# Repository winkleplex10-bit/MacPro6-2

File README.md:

# MacPro6,2

An open PCB redesign of the Mac Pro (Late 2013, "trashcan"). It keeps the enclosure, the triangular thermal core, the fan and the stock 450 W PSU, and replaces every board with new ones.

- `docs/`: the architecture spec (v0.2), the face module spec, the lineup research, the stock hardware reference and the service references
- `kicad/`: KiCad projects (the round base board/backplane, the CPU carrier fallback)
- `mechanical/`: board outlines (DXF), scan traces and 3D-print test parts

Status: early design. The CPU board is our own LGA1700 socket board with an Apple-style contact frame. The faces are an open module spec (GPU on Face P, storage on Face S).

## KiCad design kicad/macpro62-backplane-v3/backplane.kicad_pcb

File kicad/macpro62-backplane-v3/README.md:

# MacPro6,2 backplane (BP) - KiCad 9 project, rev v3 (6 layers, slot B x4; rev A1 4L history below)

## Rev v3 (2026-10-09, routed on 6 layers, slot B full x4)

- **Stackup:** 6L JLC06161H-2116, 1.6 mm, ENIG. Layers: L1 `L1_SIG_RX` (RX microstrip), L2 `L2_GND`, L3 `L3_SIG_TX_PWR` (TX stripline + `L3_3V3_SB` plane, y >= 116.2), L4 `L4_SIG_SLOTB` (new slot-B layer), L5 `L5_GND`, L6 `L6_GND_BRK` (GND + low-speed breakout). Through vias 0.45 / 0.25 only. Clearance 0.1 mm (0.15 mm for power).
- **Impedance** (`docs/impedance_v3_6L.json`, `tools/zsolve.py`):
  - L1/L6 85 Ω pairs: 85.5 Ω (w 0.26 / gap 0.125).
  - Existing v1 L3 TX pairs keep their geometry: 88.7–89.7 Ω, within ±10 %.
  - New L3/L4 pairs: 84.5–85.7 Ω (w 0.24 / gap 0.127).
- **Slot B (J1 → J10), lanes 4–7 + REFCLK1.** Intra-pair skew is 0.000 mm on all nine pairs, with 0 P/N issues (`work/pairchk.py`). Length per net and vias per net:

  | Pair | Length (mm) | Vias per net |
  |---|---|---|
  | REFCLK1 | 32.34 | 4 |
  | RX4 | 38.94 | 0 |
  | RX5 | 69.75 | 3 |
  | RX6 | 44.75 | 0 |
  | RX7 | 40.09 | 2 |
  | TX4 | 49.53 | 3 |
  | TX5 | 57.46 | 3 |
  | TX6 | 65.02 | 4 |
  | TX7 | 42.54 | 2 |

- **Broadside rule:** no low-speed track on L3 sits over L4 high-speed copper, and none on L4 sits under L3 high-speed copper (overlap 0, `work/bside.py`).
- **Copper carried over from v1:** v1 HS/SATA/USB2 copper is item-for-item identical to the slot-B build (v6_E8). The v1 48-pair skew table is unchanged (`work/skew_v1_baseline.txt`).
- **Status:**
  - `backplane.kicad_pcb`: **DRC 0 violations, 0 unconnected, 0 schematic-parity issues** (`drc_report.txt`).
  - **ERC: 0 errors / 0 warnings** (`erc_report.txt`).
  - JLC outputs in `jlc/`: 18 Gerber/drill files (6 copper layers), 44 BOM lines, 143 placed parts, all on F.
  - New parts vs A1: Q12 2N7002, R64 1 k, R65 10 k.
- **Low-speed flow:** the low-speed copper was rebuilt as follows. Step log: `PROGRESS_V3.md`.
  1. Freerouting runs, using `tools/bp_ls6.py` (the `L25=` option allows local L2/L5 routing with 0.6 mm clearance to HS copper).
  2. Single-net clean-up with `tools/bp_fix.py` and `work/reach.py`, a 0.1 mm grid min-cost router.
  3. `bp_post.sh`.
  4. DRC fix-ups, one net at a time.
- **Needs Aidan's approval before ordering:**
  - ICD 3.1 FS-lane reversal.
  - INA226 replacing INA228.
  - J7 M.2 DNP, which sets the BIOS/OpenCore boot location.
  - R27 → R33.
  - RP2350B GPIO re-map (firmware pin-map update, `tools/gpio_map.json`).
  - The U1 / Y1 / U2 moves.
  - Storage-face deviations: D-2X-1 and D-2X-2 (pending), and D-S1.
- **Interface:** ICD v3 is `/workspace/macpro62-interface-control-v3.md` (13 reserved pins).
- **Cost:** `/workspace/macpro62-cost-estimate.md` §11. Excluding the CPU, the change is about +$25–35 (6L fab). Including the CPU, it is about −$52 to +$102.
- **Previews:** `docs/preview_v3_L1.png`, `docs/preview_v3_L3.png`, `docs/preview_v3_L4.png`, `docs/preview_v3_L6.png`.

## Rev A1 (2026-10-04, routed on 4 layers)

- **Stackup:** 4L JLC04161H-7628, 1.6 mm, ENIG (was 6L JLC06161H-2116). L1 `L1_SIG_RX` (host RX, microstrip 85 Ω, 83.1 Ω calc), L2 `L2_GND`, L3 `L3_SIG_TX_PWR` (host TX stripline 86.4 Ω + `L3_3V3_SB` plane), L4 `L4_GND_BRK` (GND + low-speed breakout). Through vias 0.45 / 0.25 only. Impedance: `docs/impedance_A1.json`; loss budget: `docs/loss_budget_A1.md`. Gen5 redrivers removed (Gen4 loss 9.5–16.8 dB of 28 dB).
- **Status:** `backplane.kicad_pcb` **DRC 0 violations, 0 unconnected, 0 schematic-parity issues** (`drc_report.txt`); **ERC 0 errors / 0 warnings** (`erc_report.txt`). JLC outputs in `jlc/` (16 Gerber/drill files, 44 BOM lines, 140 placed parts, all on F; 152 footprints incl. 9 DNP).
- **High-speed pairs:** all 40 FP/FS PCIe pairs (x16 + x4, TX and RX) + FP/FS REFCLK: intra-pair skew 0.000 mm, 2 vias per net (J1 escape + one layer change). **SATA0_RX** (J7 41/43 → J1): coupled 85 Ω pair, L1 → L3, 29.45 / 29.45 mm, 2/2 vias. **SATA0_TX** (J7 47/49 → J1 A73/A74): coupled pair, L1 stubs → L3 → L1, 27.70 / 27.70 mm, 2/2 vias. **USB2_SPARE** (J1 B79/B80 → J6 13/14): coupled 90 Ω pair, 57.04 / 57.04 mm, 4/4 vias (was 15/12). USB2 (net-by-net routed, skew incl. 1.6 mm per via): USB2_FACEP 78.6/78.3 mm, skew 0.34 mm, 2/2 vias; USB2_FACES 118.0/114.8 mm, skew 0.00 (4/6 vias); USB2_MCU 28.7/28.3 mm, skew −2.7 mm (3/5 vias, could not reach ≤ 1.5 mm).
- **Flow (tools/):** `build_bp.py` → `bp_hs.py` (HS patterns) → `bp_tune.py` (skew → 0; `TUNE_RE`) → Freerouting (low-speed) → `bp_fix.py route` (grid A* clean-up; footprint/board keep-outs dilated `KOD`, NPTH clearance `NPTHC`, SATA/USB2_SPARE protected via `HSX`; `drcfix` mode removes DRC-violating copper) → `bp_pair.py` (coupled-pair centre-line A* router, `PAIR=RX|TX|USB2_SPARE`) and `bp_hand.py` (hand-route spec with clearance check) → `bp_post.sh` / `bp_finish.py` (pours, GND fan-out, DRC) → `bp_clean2.py` (in-process dangling clean-up, refills first) / `bp_island.py` (GND island stitch vias) / `bp_fill.py` → `jlc_out.py`. Skew report `bp_skew.py`, zone report `bp_zreport.py`. Step log: `PROGRESS_A1.md`.
- **Needs Aidan's approval before ordering:** ICD 3.1 FS-lane reversal; INA226 replacing INA228; J7 M.2 DNP (and so the BIOS/OpenCore boot location); R27 → R33; RP2350B GPIO re-assignment (**firmware pin-map update needed**, `tools/gpio_map.json`); the U1 / Y1 / U2 moves.
- Cost: `/workspace/macpro62-cost-estimate.md` §6a (BP q1 $285–450 → $145–230, q5 $450–750 → $260–395).
- Previews: `docs/preview_A1_L1.png` (L1), `docs/preview_A1_L3.png` (L3) (also in `work/`).

## History (floorplan revisions)

Topology: **HUB** (Aidan, 2026-10-01). The CPU board plugs into J1 (Amphenol Mini Cool Edge 224, ME1022410103011, vertical SMT) and the BP routes PCIe x16 to J9 (MCIO 124, Face P) and x4 to J10 (MCIO 124, Face S).

**Floorplan rev A-fp3 (2026-10-01):** uses Aidan's measurements M1 (GPU-board bottom edges ~15 mm above the BP) and M2 (GPU-board planes ~55 mm from the centre). J9/J10 are now **right-angle** MCIO 124 placeholders (`MP62_MCIO_124P_RightAngle_SMT_PLACEHOLDER`, est. ~9-10 mm high; straight plugs are 15.90 mm and do not fit) with the cable exiting radially under each face edge. J1 sits at the **estimated stock riser-slot chord y = -12.6** (TBD, M2b). The M.2, power and harness connectors moved to the PSU side (-y). The previous fp2 (d = 30 assumed) is archived in `variants/hub_fp2_d30_assumed/`.
**fp3a (2026-10-01, CPU-carrier cross-check):** the J1 placeholder had contact A1 at +x with the A row toward +y, which no real Mini Cool Edge has (top view, A row up: A1 is at -x). The placeholder now uses the real contact offsets from the Amphenol card drawing (incl. key F), and **J1 is rotated 180 deg**: A1 stays at disc +x (bay -> face mapping unchanged), the **A row (host TX) faces the PSU side** and the B row (host RX) faces the core. Layer use swaps: host RX on L1, host TX via to L6. Mates `/workspace/kicad/macpro62-cpu-carrier/` J1 fingers. The pre-fix state is in `/workspace/scratch/bp_before_fp3a/`.

**fp6 (2026-10-04 ≈ 09:10 ET, ICD rev 3, O-10 approved by Aidan):** zero-jog straight-straight MCIO cable with **narrow plugs**.
- `tools/hub_floorplan.py`: **J9 r_c 31.2 → 33.0, s −5.2 → +5.0** (origin (20.62, 13.27) → (14.68, 21.75), ≈ 10.4 mm); **J10 r_c 31.5 → 29.5, s −2.0 → +5.0** (origin (−15.74, 18.57) → (−19.28, 12.20), ≈ 7.3 mm). s = +5.0 = module J_PCIE X 47.0 (face spec update 6), so neither cable jogs. Narrow-plug courtyard (±21.6, `make_footprints.py` in the face template): J9–J10 gap 4.28 mm, **J1–J10 2.33 mm**, J1–J9 11.88 mm.
- **J3 (Face P AUX) (0, 51.4) rot 0 → (42.5, 13.5) rot 45** (≈ 55 mm; beyond J9's outer end, Face-P s ≈ −20.5) and **J4 (Face S AUX) (−38.0, 2.5) rot 135 → (−2.5, 43.5) rot 45** (≈ 54 mm; apex wedge, Face-S s ≈ −28.6). A full free-space search found no other GH15 site; each AUX cable runs along its own face's bottom edge above the MCIO ribbon (≈ 56 mm lateral Face P, ≈ 64 mm Face S; lengths M9).
- **U3 (0, 41.6) → (−7.5, 49.0)** (≈ 10.5 mm). Redriver row **U10–U14 +2.5 mm in x** (U14 (−19.35, −3.5) → (−16.85, −3.5), 0.51 mm to J10).
- New F.Cu rule areas `MCIO_RIBBON_J9` / `MCIO_RIBBON_J10` (no footprints/pads) from the courtyard outer edge to n 63, s ± 21.6.
- Not routed (placeholders only), so nothing to re-route. Fit check ALL OK (27 parts), **DRC 0 violations / 0 unconnected**. System fit check `tools/fitcheck_o10.py` → `fitcheck_mcio_o10.txt` (ALL OK; notes: bend beyond the BP rim r ≤ 65.8 → base ring M1b; S5 under the J9 ribbon, CR-BP-1). Previous fp5 board/scripts: `/workspace/scratch/o10/`.

**fp5 (2026-10-02 ≈ 13:15 ET, ICD rev 2, Aidan: face normals ≈ 45° / 135°):**
- `tools/hub_floorplan.py` (`FACE_P_ANG` / `FACE_S_ANG`): J9 at r_c 31.2, s −5.2, rot −45°; J10 at r_c 31.5, s −2.0, rot +45° (apex gap 1.3 mm). At 90° between faces both receptacles cannot sit at s = +8.5 (they collide at the apex; J10 is bounded by the G1 keep-out), so **CR-2 is closed by a flat-twinax jog cable** (jogs 13.7 / 10.5 mm, face spec §3.6, feasibility ICD O-6).
- J3 (0, 51.4) apex wedge; J4 (−38.0, 2.5) rot 135° beyond J10's lower-left end (6.3 mm from G1). Redrivers U10–U14, U1 (0, 15.3), U2 (−9, 6), Y1 (−2.6, 6), U3 (0, 41.6) re-packed in the V; SW1 (30.5, −34) and J8 (−40, −34) moved to the PSU side.
- `build_pcb.py` chords at 45° / 135°; drawings (corridors, plane triangle incentre (0, 24.8), lane estimate Face P 39–65 mm / Face S 40–43 mm) updated.
- CPU-LINK **A105 = PWR_ALERT#** (was RSVD_LS1; CB INA228 + eFuse FLT#, BP 10k pull-up); schematic stubs `MOD_PWR_ALERT_N`, `PWR_ALERT_BP_N`, BP INA228 0x40 note, LPT + EMC2101 reload text on the MCU sheet.
- Fit check ALL OK (27 parts, max r 57.8), DRC 0/0, ERC 0.

**fp4 (2026-10-02, interface audit, `/workspace/macpro62-interface-control.md`):**
- **CR-BP-1 applied:** the six small stock holes S1-S6 (base-board scan, `bracket/base_board/`) get D6 rule-area keep-outs (`CR-BP-1_KO_S1..S6`, all copper layers, no footprints/tracks/vias/pours) and are part of the fit check (courtyard >= 3.0 mm from each S centre). **U4** moved from (-27, -46.5) (S2 inside its courtyard) to (-30, -38). **J6** moved to x 11.4 (S3), **J3** to the apex V at (0, 51) rot 0 and **J4** parallel to the J10 inner side at (-15.9, 14.95) rot 60 (S4/S5 and the new J9 position); **J8** SWD to (0, 44.6), **U3** to (0, 39.8), **Y1** to (-6.4, 14.0).
- **J3/J4 are GH 15P** (`JST_GH_BM15B-GHS-TBT`, face spec C-4: pin 15 MOD_LED#, pins 13/14 USB2 primary); pinout 1:1 with `macpro62-face/pinouts/mp62-face-v0.1_aux_gh15.csv`.
- **J9/J10 use the SFF-TA-1016 RA footprint** `MP62_MCIO_124P_RA_SFF-TA-1016` (copied from the face template by `make_placeholders.py`). CR-2 (s = +8.5 on both faces) is **only partly possible**: J9 at s = +8.0 / r_c 36.5 (0.5 mm short, S5 keep-out); J10 at s > -4.6 enters the G1 gold-hole keep-out (6 mm), so it stays at s = -5.0 / r_c 37.2 and the **Face S cable needs a 13.5 mm lateral jog** (open decision, ICD O-1).
- **J5 (fan GH4) removed:** the fan is driven by the IOB EMC2101 (0x4C, I2C_SYS) on IOB CONN_C; the BP MCU writes the CB fan demand (CPU-LINK FAN_PWMOUT) to it. `fan.kicad_sch` deleted.
- **Schematic stubs** gained IOB-LINK `IOB_INT_N`, `IOB_PRSNT_N`, `IOB_USB_DP/DN` (CPU-LINK USB2_SPARE), face `MOD_LED_N`, CPU-LINK `MOD_I2C0` (CB ID EEPROM 0x57); each stub sheet now holds one non-BOM `#BLKn` symbol (passive pins, `MP62_BP_Stubs.kicad_sym`) so **ERC is 0 violations**.
- `docs/cpulink_224_pinout_draft.csv` has a **CB mapping column** (LGA1700/Z790 PCH + RP2350 EC net, direction seen from the CB).

Spec: `/workspace/macpro62-architecture-spec-v0.2.md` (sections 3 and 4.9). Interfaces: `/workspace/macpro62-interface-control.md`.

| File | What |
|---|---|
| `backplane.kicad_pcb` / `.kicad_pro` | HUB floorplan, 6 layers, JLC06161H-2116 stackup, placeholders only (not routed) |
| `floorplan.png` / `.svg` | Render of the hub floorplan |
| `drc_report.txt` | `kicad-cli pcb drc --severity-all`: 0 violations, 0 unconnected |
| `fitcheck_floorplan.txt` | r_max <= 58 mm, gold-hole distance >= 6 mm and S1-S6 distance >= 3 mm per footprint |
| `fitcheck_mcio_o10.txt` | O-10 system fit check (`tools/fitcheck_o10.py`, system python3): zero jog, J1 clearance, ribbon corridors, cable lengths, face envelope, SM-1 |
| `lane_length_estimate.txt` | Estimated BP PCIe lane lengths (J1 -> MCIO) |
| `docs/cpulink_224_pinout_draft.csv` | CPU-LINK 224 pin list draft with the CB mapping (from `tools/cpulink_pinout.py`) |
| `backplane_direct.kicad_pcb` | Saved DIRECT variant (4L JLC04161H-7628, no PCIe on BP) |
| `variants/` | Direct fit check, DRC and render; archived all-MCIO hub fit check; `hub_fp2_d30_assumed/` (previous hub floorplan) |
| `backplane.kicad_sch` + sheets | Block-diagram stubs (hierarchical labels + non-BOM stub symbols); `erc_report.txt`: 0 violations |
| `MP62_Placeholders.pretty/` | Placeholder footprints (outer dimensions from vendor drawings) + the SFF-TA-1016 MCIO RA footprint |
| `MP62_BP_Stubs.kicad_sym`, `sym-lib-table` | Stub symbols written by `tools/build_sch.py` |

Rebuild (from this folder):

```
python3 tools/make_placeholders.py
rm -f backplane.kicad_pcb backplane.kicad_pro backplane.kicad_prl
python3 tools/build_pcb.py          # VARIANT=direct for backplane_direct.kicad_pcb
python3 tools/postprocess.py        # VARIANT=direct for the 4L stackup
kicad-cli pcb drc --severity-all -o drc_report.txt backplane.kicad_pcb
tools/render.sh backplane.kicad_pcb floorplan
python3 tools/fitcheck_o10.py       # needs ../macpro62-face-template and ../macpro62-storage-face
python3 tools/cpulink_pinout.py
python3 tools/build_sch.py
kicad-cli sch erc --severity-all -o erc_report.txt backplane.kicad_sch
```

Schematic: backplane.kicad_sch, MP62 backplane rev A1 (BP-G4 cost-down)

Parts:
C1, C5, C8, C9, C12, C14, C16, C19, C21, C22, C23, C24, C25, C26, C27, C28, C32, C33, C34, C35, C38, C39: 100nF 16V X7R 0402; C_0402_1005Metric; LCSC C1525
C2, C3, C4, C6, C7, C10, C11, C13, C15: 22uF 25V X5R 0805; C_0805_2012Metric; LCSC C45783
C17: 22uF 25V X5R 0805; C_0805_2012Metric; LCSC C45783; not fitted
C18: 100nF 16V X7R 0402; C_0402_1005Metric; LCSC C1525; not fitted
C20: 1uF 25V X5R 0402; C_0402_1005Metric; LCSC C52923
C29, C30, C31: 4.7uF 10V X5R 0402; C_0402_1005Metric; LCSC C23733
C36, C37: 15pF 50V C0G 0402; C_0402_1005Metric; LCSC C1548
D1, D2: SS34 3A 40V Schottky SMA; D_SMA; LCSC C8678
D3: SMAJ15A TVS SMA; D_SMA; LCSC C113958
D4, D5: BAT54A (LBAT54ALT1G); SOT-23; LCSC C12743
D6, D7, D8, D9, D10: LED red 0603; LED_0603_1608Metric; LCSC C2286
F1: 3A 1206 fast fuse (0466003.NRHF class); Fuse_1206_3216Metric; LCSC C14165
H1, H2: MountingHole D4 plated (GND); MountingHole_4mm_Pad
H3: M.2 2242 standoff pad (DNP option); MP62_M2_Standoff_SMT_M2_Pad5.0; not fitted
J1: ME1022410103011 Mini Cool Edge 224 (C4941560, 0 s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; MP62_CPULINK_MiniCoolEdge_224P_Vertical_SMT_PLACEHOLDER; LCSC C4941560
J2: Molex 43045-0812 Micro-Fit 2x4 (C277661); Molex_Micro-Fit_3.0_43045-0812_2x04_P3.00mm_Vertical; LCSC C277661
J3: BM15B-GHS-TBT (C5305069) Face P AUX; JST_GH_BM15B-GHS-TBT_1x15-1MP_P1.25mm_Vertical; LCSC C5305069
J4: BM15B-GHS-TBT (C5305069) Face S AUX; JST_GH_BM15B-GHS-TBT_1x15-1MP_P1.25mm_Vertical; LCSC C5305069
J6: BM15B-GHS-TBT (C5305069) IOB-LINK; JST_GH_BM15B-GHS-TBT_1x15-1MP_P1.25mm_Vertical; LCSC C5305069
J7: M.2 M-key socket LOTES APCI0107 class (C841661) -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; MP62_M2_MKey_SMT_H4.2_PLACEHOLDER; LCSC C841661; not fitted
J8: BM03B-SRSS-TB SWD (DNP); JST_SH_BM03B-SRSS-TB_1x03-1MP_P1.00mm_Vertical; LCSC C160389; not fitted
J9: MCIO 124P RA G97R24332HR class (C4867471, 0 stock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; MP62_MCIO_124P_RA_SFF-TA-1016; LCSC C4867471
J10: MCIO 124P RA (C4867471) -> Face S x4 + slot B x4 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; MP62_MCIO_124P_RA_SFF-TA-1016; LCSC C4867471
JP1: BENCH: bridges the Hall interlock (open = normal); SolderJumper-2_P1.3mm_Open_RoundedPad1.0x1.5mm
L1, L2: 4.7uH 2A 4x4 (SWPA4030S4R7MT); L_Changjiang_FNR4030S; LCSC C57269
L3: 3.3uH 0806 (FNR201610S3R3MT, RP2350 VREG); L_0805_2012Metric; LCSC C167673
Q1, Q2, Q5, Q6, Q7, Q8: AO3401A P-MOS; SOT-23; LCSC C15127
Q3: AO3401A P-MOS; SOT-23; LCSC C15127; not fitted
Q4: 2N7002 N-MOS; SOT-23; LCSC C8545; not fitted
Q9, Q10, Q11, Q12: 2N7002 N-MOS; SOT-23; LCSC C8545
R1: 33k 1% 0402; R_0402_1005Metric; LCSC C25779
R2, R4, R7, R8, R13, R14, R15, R16, R17, R18, R19, R20, R21, R23, R24, R25, R26, R29, R30, R33, R34, R35, R36, R39, R40, R42, R43, R44, R45, R46, R47, R48, R49, R65: 10k 1% 0402; R_0402_1005Metric; LCSC C25744
R3: 56k 1% 0402; R_0402_1005Metric; LCSC C25796
R5: 100k 1% 0402 (U6 EN, always on); R_0402_1005Metric; LCSC C25741
R6: 100k 1% 0402 (U7 off until the MCU enables 5V_SBY); R_0402_1005Metric; LCSC C25741
R9, R10: 10k 1% 0402; R_0402_1005Metric; LCSC C25744; not fitted
R11, R12, R55: 100k 1% 0402; R_0402_1005Metric; LCSC C25741
R22, R31, R32, R41, R54, R58, R60, R61, R64: 1k 1% 0402; R_0402_1005Metric; LCSC C11702
R27, R28, R37, R38, R50, R51, R52, R53: 2.2k 1% 0402; R_0402_1005Metric; LCSC C25879
R56: 10k 1% 0402 (12V LED); R_0402_1005Metric; LCSC C25744
R57: 10k 1% 0402 (11V_SB LED); R_0402_1005Metric; LCSC C25744
R59, R62, R63: 33R 1% 0402; R_0402_1005Metric; LCSC C25105
R100: 10mR 1% 1W 1206 shunt; R_1206_3216Metric; LCSC C105362
SW1: BOOTSEL (TS-1187A); SW_Push_1P1T_XKB_TS-1187A; LCSC C318884
SW2: BENCH power button (TS-1187A); SW_Push_1P1T_XKB_TS-1187A; LCSC C318884
U1: RP2350B QFN-80 (C42415655); QFN-80-1EP_10x10mm_P0.4mm_EP3.4x3.4mm; LCSC C42415655
U2: W25Q128JVSIQ (C97521, basic); SOIC-8_5.3x5.3mm_P1.27mm; LCSC C97521
U3: TMP1075DGKR @0x48 core side (C2864807); VSSOP-8_3x3mm_P0.65mm; LCSC C2864807
U4: TMP1075DGKR @0x49 PSU side (C2864807); VSSOP-8_3x3mm_P0.65mm; LCSC C2864807
U5: INA226AIDGSR @0x40 (C49851); VSSOP-10_3x3mm_P0.5mm; LCSC C49851
U6: TPS563201DDCR (C116592) -> 3V3_SB; SOT-23-6; LCSC C116592
U7: TPS563201DDCR (C116592) -> 5V_SBY; SOT-23-6; LCSC C116592
U8: SN74LVC1G74DCUR thermal latch (C70285); VSSOP-8_2.3x2mm_P0.5mm; LCSC C70285
Y1: 12MHz 3225 crystal 20pF; Crystal_SMD_3225-4Pin_3.2x2.5mm; LCSC C9002

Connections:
3V3_AUX_P: C13.1, C14.1, J3.1 (3V3_AUX), J3.2 (3V3_AUX), Q1.3 (D), R26.2, R27.2, R28.2, R29.2, R30.2, R31.2
3V3_AUX_S: C15.1, C16.1, J4.1 (3V3_AUX), J4.2 (3V3_AUX), Q2.3 (D), R36.2, R37.2, R38.2, R39.2, R40.2, R41.2, R65.2
3V3_M2: C17.1, C18.1, J7.2 (3V3), J7.4 (3V3), J7.12 (3V3), J7.14 (3V3), J7.16 (3V3), J7.18 (3V3), J7.70 (3V3), J7.72 (3V3), J7.74 (3V3), Q3.3 (D)
3V3_SB: C1.1, C6.1, C7.1, C19.1, C21.1, C22.1, C23.1, C24.1, C25.1, C26.1, C27.1, C28.1, C29.1, C38.1, D10.2 (A), J1.B107 (3V3_SB), J1.B108 (3V3_SB), J6.1 (3V3_SB), J6.2 (3V3_SB), JP1.1, L1.2, Q1.2 (S), Q2.2 (S), Q3.2 (S), Q5.2 (S), Q6.2 (S), R1.1, R7.2, R8.2, R9.2, R13.2, R14.2, R15.2, R16.2, R17.2, R18.2, R19.2, R20.2, R21.2, R23.2, R24.2, R25.2, R33.2, R34.2, R35.2, R42.2, R43.2, R44.2, R45.2, R46.2, R47.2, R48.2, R49.2, R50.2, R51.2, R52.2, R53.2, R59.1, U1.5 (IOVDD), U1.15 (IOVDD), U1.24 (IOVDD), U1.29 (IOVDD), U1.41 (IOVDD), U1.50 (IOVDD), U1.59 (ADC_AVDD), U1.60 (IOVDD), U1.64 (VREG_VIN), U1.68 (USB_OTP_VDD), U1.69 (QSPI_IOVDD), U1.76 (IOVDD), U2.8 (VCC), U3.8 (V+), U4.7 (A0), U4.8 (V+), U5.6 (VS), U8.8 (VCC)
5V_SBY: C10.1, C11.1, J1.A107 (5V_SBY), J1.A108 (5V_SBY), J1.A110 (5V_SBY), J1.A111 (5V_SBY), J1.B110 (5V_SBY), J1.B111 (5V_SBY), L2.2, R3.1
11V_SB_IN: D2.2 (A), D9.2 (A), J2.7 (11V_SB)
12V_MAIN_IN: D1.2 (A), D8.2 (A), J2.1 (12V_MAIN), J2.2 (12V_MAIN)
AUXP_EN_N: Q1.1 (G), R7.1, U1.37 (GPIO29)
AUXS_EN_N: Q2.1 (G), R8.1, U1.19 (GPIO19)
BOOTSEL_N: R61.2, SW1.1
BP_OTEMP_N: D5.2 (K2), R21.1, U3.3 (ALERT), U4.3 (ALERT)
BST_3V3_SB: C5.1, U6.6 (VBST)
BST_5V_SBY: C9.1, U7.6 (VBST)
CB_CARRIER_HOT_N: J1.A98 (CARRIER_HOT#), R44.1, U1.13 (GPIO14)
CB_FAN_PWM: J1.B96 (FAN_PWMOUT), U1.6 (GPIO8)
CB_FAN_TACH: J1.B98 (FAN_TACHIN), U1.2 (GPIO5)
CB_I2C0_SCL: J1.B90 (I2C0_CLK), R50.1, U1.80 (GPIO3)
CB_I2C0_SDA: J1.B92 (I2C0_DAT), R51.1, U1.79 (GPIO2)
CB_PLTRST_N: J1.A95 (PLTRST#), R22.1, R32.1, R64.1, U1.54 (GPIO43)
CB_PWRBTN_N: J1.B99 (PWRBTN#), R42.1, U1.57 (GPIO46)
CB_PWR_ALERT_N: J1.A105 (PWR_ALERT#), R43.1, U1.12 (GPIO13)
CB_RSMRST_N: J1.A92 (RSMRST_OUT#), U1.16 (GPIO16)
CB_SUS_S3_N: J1.A89 (SUS_S3#), Q4.1 (G), U1.21 (GPIO21)
CB_SUS_S45_N: J1.A90 (SUS_S4_S5#), U1.58 (GPIO47)
CB_THERMTRIP_N: D4.1 (K1), J1.A96 (THERMTRIP#), R18.1
CB_UART0_RX: J1.B95 (UART0_RX), U1.78 (GPIO1)
CB_UART0_TX: J1.B93 (UART0_TX), U1.77 (GPIO0)
CB_VIN_PWR_OK: J1.A93 (VIN_PWR_OK), U1.14 (GPIO15)
CB_WAKE_N: J1.A99 (WAKE0#), J10.A9 (WAKE), J10.A27 (WAKE1)
CC_PRSNT1_N: J1.A1 (CC_PRSNT1#), R45.1, U1.53 (GPIO42)
CC_PRSNT2_N: J1.A112 (CC_PRSNT2#), R46.1, U1.11 (GPIO12)
DVDD: C30.1, C31.1, C32.1, C33.1, C34.1, L3.2, U1.10 (DVDD), U1.32 (DVDD), U1.51 (DVDD), U1.65 (VREG_FB)
EN_3V3: R5.1, U6.5 (EN)
EN_5V: R6.1, U1.40 (GPIO32), U7.5 (EN)
FB_3V3_SB: R1.2, R2.1, U6.4 (VFB)
FB_5V_SBY: R3.2, R4.1, U7.4 (VFB)
FP_HOLD: Q10.1 (G), R23.1, U1.36 (GPIO28)
FP_LEDA: D6.2 (A), R31.1
FP_MCIO_PRSNT_N: J9.B12 (PRSNT), R24.1, U1.47 (GPIO38)
FP_MOD_LED_N: D6.1 (K), J3.15 (MOD_LED#)
FP_PERST_N: J9.B11 (PERST), Q10.3 (D), R22.2
FP_PRSNT_N: J3.4 (FACE_PRSNT#), R25.1, U1.42 (GPIO33)
FP_PWR_EN: J3.5 (FACE_PWR_EN), U1.49 (GPIO40_ADC0)
FP_PWR_GOOD: J3.6 (FACE_PWR_GOOD), R26.1, U1.43 (GPIO34)
FP_REFCLK_N: J1.A52 (FP_REFCLK_N), J9.A12 (REFCLK-)
FP_REFCLK_P: J1.A51 (FP_REFCLK_P), J9.A11 (REFCLK+)
FP_RX0_N: J1.B49 (FP_PER0_N), J9.A3 (PER0N)
FP_RX0_P: J1.B48 (FP_PER0_P), J9.A2 (PER0P)
FP_RX1_N: J1.B46 (FP_PER1_N), J9.A6 (PER1N)
FP_RX1_P: J1.B45 (FP_PER1_P), J9.A5 (PER1P)
FP_RX2_N: J1.B43 (FP_PER2_N), J9.A15 (PER2N)
FP_RX2_P: J1.B42 (FP_PER2_P), J9.A14 (PER2P)
FP_RX3_N: J1.B40 (FP_PER3_N), J9.A18 (PER3N)
FP_RX3_P: J1.B39 (FP_PER3_P), J9.A17 (PER3P)
FP_RX4_N: J1.B37 (FP_PER4_N), J9.A21 (PER4N)
FP_RX4_P: J1.B36 (FP_PER4_P), J9.A20 (PER4P)
FP_RX5_N: J1.B34 (FP_PER5_N), J9.A24 (PER5N)
FP_RX5_P: J1.B33 (FP_PER5_P), J9.A23 (PER5P)
FP_RX6_N: J1.B31 (FP_PER6_N), J9.A33 (PER6N)
FP_RX6_P: J1.B30 (FP_PER6_P), J9.A32 (PER6P)
FP_RX7_N: J1.B27 (FP_PER7_N), J9.A36 (PER7N)
FP_RX7_P: J1.B26 (FP_PER7_P), J9.A35 (PER7P)
FP_RX8_N: J1.B24 (FP_PER8_N), J9.A40 (PER8N)
FP_RX8_P: J1.B23 (FP_PER8_P), J9.A39 (PER8P)
FP_RX9_N: J1.B21 (FP_PER9_N), J9.A43 (PER9N)
FP_RX9_P: J1.B20 (FP_PER9_P), J9.A42 (PER9P)
FP_RX10_N: J1.B18 (FP_PER10_N), J9.A46 (PER10N)
FP_RX10_P: J1.B17 (FP_PER10_P), J9.A45 (PER10P)
FP_RX11_N: J1.B15 (FP_PER11_N), J9.A49 (PER11N)
FP_RX11_P: J1.B14 (FP_PER11_P), J9.A48 (PER11P)
FP_RX12_N: J1.B12 (FP_PER12_N), J9.A52 (PER12N)
FP_RX12_P: J1.B11 (FP_PER12_P), J9.A51 (PER12P)
FP_RX13_N: J1.B9 (FP_PER13_N), J9.A55 (PER13N)
FP_RX13_P: J1.B8 (FP_PER13_P), J9.A54 (PER13P)
FP_RX14_N: J1.B6 (FP_PER14_N), J9.A58 (PER14N)
FP_RX14_P: J1.B5 (FP_PER14_P), J9.A57 (PER14P)
FP_RX15_N: J1.B3 (FP_PER15_N), J9.A61 (PER15N)
FP_RX15_P: J1.B2 (FP_PER15_P), J9.A60 (PER15P)
FP_SMB_ALERT_N: J3.10 (FACE_SMB_ALERT#), R29.1, U1.44 (GPIO35)
FP_SMB_SCL: J3.8 (FACE_SMB_CLK), R27.1, U1.56 (GPIO45)
FP_SMB_SDA: J3.9 (FACE_SMB_DAT), R28.1, U1.55 (GPIO44)
FP_THERM_ALERT_N: J3.11 (THERM_ALERT#), R30.1, U1.23 (GPIO23)
FP_THERM_TRIP_N: D4.2 (K2), J3.12 (THERM_TRIP#), R19.1
FP_TX0_N: J1.A49 (FP_PET0_N), J9.B3 (PET0N)
FP_TX0_P: J1.A48 (FP_PET0_P), J9.B2 (PET0P)
FP_TX1_N: J1.A46 (FP_PET1_N), J9.B6 (PET1N)
FP_TX1_P: J1.A45 (FP_PET1_P), J9.B5 (PET1P)
FP_TX2_N: J1.A43 (FP_PET2_N), J9.B15 (PET2N)
FP_TX2_P: J1.A42 (FP_PET2_P), J9.B14 (PET2P)
FP_TX3_N: J1.A40 (FP_PET3_N), J9.B18 (PET3N)
FP_TX3_P: J1.A39 (FP_PET3_P), J9.B17 (PET3P)
FP_TX4_N: J1.A37 (FP_PET4_N), J9.B21 (PET4N)
FP_TX4_P: J1.A36 (FP_PET4_P), J9.B20 (PET4P)
FP_TX5_N: J1.A34 (FP_PET5_N), J9.B24 (PET5N)
FP_TX5_P: J1.A33 (FP_PET5_P), J9.B23 (PET5P)
FP_TX6_N: J1.A31 (FP_PET6_N), J9.B33 (PET6N)
FP_TX6_P: J1.A30 (FP_PET6_P), J9.B32 (PET6P)
FP_TX7_N: J1.A27 (FP_PET7_N), J9.B36 (PET7N)
FP_TX7_P: J1.A26 (FP_PET7_P), J9.B35 (PET7P)
FP_TX8_N: J1.A24 (FP_PET8_N), J9.B40 (PET8N)
FP_TX8_P: J1.A23 (FP_PET8_P), J9.B39 (PET8P)
FP_TX9_N: J1.A21 (FP_PET9_N), J9.B43 (PET9N)
FP_TX9_P: J1.A20 (FP_PET9_P), J9.B42 (PET9P)
FP_TX10_N: J1.A18 (FP_PET10_N), J9.B46 (PET10N)
FP_TX10_P: J1.A17 (FP_PET10_P), J9.B45 (PET10P)
FP_TX11_N: J1.A15 (FP_PET11_N), J9.B49 (PET11N)
FP_TX11_P: J1.A14 (FP_PET11_P), J9.B48 (PET11P)
FP_TX12_N: J1.A12 (FP_PET12_N), J9.B52 (PET12N)
FP_TX12_P: J1.A11 (FP_PET12_P), J9.B51 (PET12P)
FP_TX13_N: J1.A9 (FP_PET13_N), J9.B55 (PET13N)
FP_TX13_P: J1.A8 (FP_PET13_P), J9.B54 (PET13P)
FP_TX14_N: J1.A6 (FP_PET14_N), J9.B58 (PET14N)
FP_TX14_P: J1.A5 (FP_PET14_P), J9.B57 (PET14P)
FP_TX15_N: J1.A3 (FP_PET15_N), J9.B61 (PET15N)
FP_TX15_P: J1.A2 (FP_PET15_P), J9.B60 (PET15P)
FS_CLKREQ1_N: J10.A26 (CLKREQ1), R65.1
FS_HOLD: Q11.1 (G), Q12.1 (G), R33.1, U1.17 (GPIO17)
FS_LEDA: D7.2 (A), R41.1
FS_MCIO_PRSNT_N: J10.B12 (PRSNT), R34.1, U1.8 (GPIO10)
FS_MOD_LED_N: D7.1 (K), J4.15 (MOD_LED#)
FS_PERST1_N: J10.B29 (PERST1), Q12.3 (D), R64.2
FS_PERST_N: J10.B11 (PERST), Q11.3 (D), R32.2
FS_PRSNT_N: J4.4 (FACE_PRSNT#), R35.1, U1.9 (GPIO11)
FS_PWR_EN: J4.5 (FACE_PWR_EN), U1.1 (GPIO4)
FS_PWR_GOOD: J4.6 (FACE_PWR_GOOD), R36.1, U1.7 (GPIO9)
FS_REFCLK1_N: J1.B102 (FS_REFCLK1_N), J10.A30 (REFCLK1-)
FS_REFCLK1_P: J1.B101 (FS_REFCLK1_P), J10.A29 (REFCLK1+)
FS_REFCLK_N: J1.A71 (FS_REFCLK_N), J10.A12 (REFCLK-)
FS_REFCLK_P: J1.A70 (FS_REFCLK_P), J10.A11 (REFCLK+)
FS_RX0_N: J1.B68 (FS_PER0_N), J10.A3 (PER0N)
FS_RX0_P: J1.B67 (FS_PER0_P), J10.A2 (PER0P)
FS_RX1_N: J1.B65 (FS_PER1_N), J10.A6 (PER1N)
FS_RX1_P: J1.B64 (FS_PER1_P), J10.A5 (PER1P)
FS_RX2_N: J1.B62 (FS_PER2_N), J10.A15 (PER2N)
FS_RX2_P: J1.B61 (FS_PER2_P), J10.A14 (PER2P)
FS_RX3_N: J1.B59 (FS_PER3_N), J10.A18 (PER3N)
FS_RX3_P: J1.B58 (FS_PER3_P), J10.A17 (PER3P)
FS_RX4_N: J1.B83 (FS_PER4_N), J10.A21 (PER4N)
FS_RX4_P: J1.B82 (FS_PER4_P), J10.A20 (PER4P)
FS_RX5_N: J1.B86 (FS_PER5_N), J10.A24 (PER5N)
FS_RX5_P: J1.B87 (FS_PER5_P), J10.A23 (PER5P)
FS_RX6_N: J1.B104 (FS_PER6_N), J10.A33 (PER6N)
FS_RX6_P: J1.B105 (FS_PER6_P), J10.A32 (PER6P)
FS_RX7_N: J1.B55 (FS_PER7_N), J10.A36 (PER7N)
FS_RX7_P: J1.B54 (FS_PER7_P), J10.A35 (PER7P)
FS_SMB_ALERT_N: J4.10 (FACE_SMB_ALERT#), R39.1, U1.52 (GPIO41)
FS_SMB_SCL: J4.8 (FACE_SMB_CLK), R37.1, U1.4 (GPIO7)
FS_SMB_SDA: J4.9 (FACE_SMB_DAT), R38.1, U1.3 (GPIO6)
FS_THERM_ALERT_N: J4.11 (THERM_ALERT#), R40.1, U1.48 (GPIO39)
FS_THERM_TRIP_N: D5.1 (K1), J4.12 (THERM_TRIP#), R20.1
FS_TX0_N: J1.A68 (FS_PET0_N), J10.B3 (PET0N)
FS_TX0_P: J1.A67 (FS_PET0_P), J10.B2 (PET0P)
FS_TX1_N: J1.A65 (FS_PET1_N), J10.B6 (PET1N)
FS_TX1_P: J1.A64 (FS_PET1_P), J10.B5 (PET1P)
FS_TX2_N: J1.A62 (FS_PET2_N), J10.B15 (PET2N)
FS_TX2_P: J1.A61 (FS_PET2_P), J10.B14 (PET2P)
FS_TX3_N: J1.A59 (FS_PET3_N), J10.B18 (PET3N)
FS_TX3_P: J1.A58 (FS_PET3_P), J10.B17 (PET3P)
FS_TX4_N: J1.A83 (FS_PET4_N), J10.B21 (PET4N)
FS_TX4_P: J1.A82 (FS_PET4_P), J10.B20 (PET4P)
FS_TX5_N: J1.A87 (FS_PET5_N), J10.B24 (PET5N)
FS_TX5_P: J1.A86 (FS_PET5_P), J10.B23 (PET5P)
FS_TX6_N: J1.A102 (FS_PET6_N), J10.B33 (PET6N)
FS_TX6_P: J1.A101 (FS_PET6_P), J10.B32 (PET6P)
FS_TX7_N: J1.A55 (FS_PET7_N), J10.B36 (PET7N)
FS_TX7_P: J1.A54 (FS_PET7_P), J10.B35 (PET7P)
GND: C1.2, C2.2, C3.2, C4.2, C6.2, C7.2, C8.2, C10.2, C11.2, C12.2, C13.2, C14.2, C15.2, C16.2, C17.2, C18.2, C19.2, C20.2, C21.2, C22.2, C23.2, C24.2, C25.2, C26.2, C27.2, C28.2, C29.2, C30.2, C31.2, C32.2, C33.2, C34.2, C35.2, C36.2, C37.2, C38.2, C39.2, D3.2 (A), H1.1, H2.1, H3.1, J1.A4 (GND), J1.A7 (GND), J1.A10 (GND), J1.A13 (GND), J1.A16 (GND), J1.A19 (GND), J1.A22 (GND), J1.A25 (GND), J1.A28 (GND), J1.A29 (GND), J1.A32 (GND), J1.A35 (GND), J1.A38 (GND), J1.A41 (GND), J1.A44 (GND), J1.A47 (GND), J1.A50 (GND), J1.A53 (GND), J1.A56 (GND), J1.A57 (GND), J1.A60 (GND), J1.A63 (GND), J1.A66 (GND), J1.A69 (GND), J1.A72 (GND), J1.A75 (GND), J1.A78 (GND), J1.A81 (GND), J1.A84 (GND), J1.A85 (GND), J1.A88 (GND), J1.A91 (GND), J1.A94 (GND), J1.A97 (GND), J1.A100 (GND), J1.A103 (GND), J1.A106 (GND), J1.A109 (GND), J1.B1 (GND), J1.B4 (GND), J1.B7 (GND), J1.B10 (GND), J1.B13 (GND), J1.B16 (GND), J1.B19 (GND), J1.B22 (GND), J1.B25 (GND), J1.B28 (GND), J1.B29 (GND), J1.B32 (GND), J1.B35 (GND), J1.B38 (GND), J1.B41 (GND), J1.B44 (GND), J1.B47 (GND), J1.B50 (GND), J1.B53 (GND), J1.B56 (GND), J1.B57 (GND), J1.B60 (GND), J1.B63 (GND), J1.B66 (GND), J1.B69 (GND), J1.B72 (GND), J1.B75 (GND), J1.B78 (GND), J1.B81 (GND), J1.B84 (GND), J1.B85 (GND), J1.B88 (GND), J1.B91 (GND), J1.B94 (GND), J1.B97 (GND), J1.B100 (GND), J1.B103 (GND), J1.B106 (GND), J1.B109 (GND), J1.B112 (GND), J1.BL (BOARDLOCK), J2.3 (GND), J2.4 (GND), J2.5 (GND), J3.3 (GND), J3.7 (GND), J3.MP, J4.3 (GND), J4.7 (GND), J4.MP, J6.3 (GND), J6.7 (GND), J6.12 (GND), J6.15 (GND), J6.MP, J7.1 (GND), J7.3 (GND), J7.9 (GND), J7.15 (GND), J7.21 (GND), J7.27 (GND), J7.33 (GND), J7.39 (GND), J7.45 (GND), J7.51 (GND), J7.57 (GND), J7.71 (GND), J7.73 (GND), J7.MP, J8.2 (GND), J8.MP, J9.A1 (GND), J9.A4 (GND), J9.A7 (GND), J9.A10 (GND), J9.A13 (GND), J9.A16 (GND), J9.A19 (GND), J9.A22 (GND), J9.A25 (GND), J9.A28 (GND), J9.A31 (GND), J9.A34 (GND), J9.A37 (GND), J9.A38 (GND), J9.A41 (GND), J9.A44 (GND), J9.A47 (GND), J9.A50 (GND), J9.A53 (GND), J9.A56 (GND), J9.A59 (GND), J9.A62 (GND), J9.B1 (GND), J9.B4 (GND), J9.B7 (GND), J9.B10 (GND), J9.B13 (GND), J9.B16 (GND), J9.B19 (GND), J9.B22 (GND), J9.B25 (GND), J9.B28 (GND), J9.B31 (GND), J9.B34 (GND), J9.B37 (GND), J9.B38 (GND), J9.B41 (GND), J9.B44 (GND), J9.B47 (GND), J9.B50 (GND), J9.B53 (GND), J9.B56 (GND), J9.B59 (GND), J9.B62 (GND), J9.MP (SHIELD), J10.A1 (GND), J10.A4 (GND), J10.A7 (GND), J10.A10 (GND), J10.A13 (GND), J10.A16 (GND), J10.A19 (GND), J10.A22 (GND), J10.A25 (GND), J10.A28 (GND), J10.A31 (GND), J10.A34 (GND), J10.A37 (GND), J10.A38 (GND), J10.A41 (GND), J10.A44 (GND), J10.A47 (GND), J10.A50 (GND), J10.A53 (GND), J10.A56 (GND), J10.A59 (GND), J10.A62 (GND), J10.B1 (GND), J10.B4 (GND), J10.B7 (GND), J10.B10 (GND), J10.B13 (GND), J10.B16 (GND), J10.B19 (GND), J10.B22 (GND), J10.B25 (GND), J10.B28 (GND), J10.B31 (GND), J10.B34 (GND), J10.B37 (GND), J10.B38 (GND), J10.B41 (GND), J10.B44 (GND), J10.B47 (GND), J10.B50 (GND), J10.B53 (GND), J10.B56 (GND), J10.B59 (GND), J10.B62 (GND), J10.MP (SHIELD), Q4.2 (S), Q9.2 (S), Q10.2 (S), Q11.2 (S), Q12.2 (S), R2.2, R4.2, R6.2, R10.2, R11.2, R12.2, R55.2, R56.2, R57.2, SW1.2, SW2.2, U1.62 (VREG_PGND), U1.81 (GND_EP), U2.4 (GND), U3.4 (GND), U3.5 (A2), U3.6 (A1), U3.7 (A0), U4.4 (GND), U4.5 (A2), U4.6 (A1), U5.1 (A1), U5.2 (A0), U5.7 (GND), U6.1 (GND), U7.1 (GND), U8.1 (CLK), U8.2 (D), U8.4 (GND), Y1.2 (GND), Y1.4 (GND)
HALL_A_N: J6.5 (HALL_A_N), Q5.1 (G), R13.1
HALL_B_N: J6.6 (HALL_B_N), Q6.1 (G), R14.1
I2C_SYS_SCL: J6.8 (I2C_SYS_SCL), R52.1, U1.46 (GPIO37), U3.2 (SCL), U4.2 (SCL), U5.5 (SCL)
I2C_SYS_SDA: J6.9 (I2C_SYS_SDA), R53.1, U1.45 (GPIO36), U3.1 (SDA), U4.1 (SDA), U5.4 (SDA)
ILK_A: JP1.2, Q5.3 (D), Q6.3 (D), Q7.2 (S), R11.1, U1.38 (GPIO30)
ILK_B: Q7.3 (D), Q8.2 (S)
IOB_PRSNT_N: J6.11 (IOB_PRSNT_N), R48.1, U1.22 (GPIO22)
LATCH_CLR_N: C20.1, R16.1, U1.28 (GPIO27), U8.6 (CLR#)
LED11_K: D9.1 (K), R57.1
LED12_K: D8.1 (K), R56.1
LED_ST_K: D10.1 (K), R58.1
M2_DEVSLP: J7.38 (DEVSLP), R10.1
M2_EN_N: Q3.1 (G), Q4.3 (D), R9.1
MCU_LED_N: R58.2, U1.18 (GPIO18)
MCU_RUN: C39.1, U1.35 (RUN)
MCU_SWCLK: J8.1 (SWCLK), U1.33 (SWCLK)
MCU_SWDIO: J8.3 (SWDIO), U1.34 (SWDIO)
PSON_DRV: Q8.3 (D), Q9.1 (G), R12.1
PSU_PS_ON_N: J2.6 (PS_ON#), Q9.3 (D)
PSU_PWR_OK: J2.8 (PWR_OK), R54.1
PSU_PWR_OK_M: R54.2, R55.1, U1.20 (GPIO20)
PS_ON_REQ_N: Q7.1 (G), R15.1, U1.39 (GPIO31)
PWRBTN_IN_N: J6.4 (PWRBTN_IN_N), R49.1, SW2.1, U1.25 (GPIO24)
QSPI_SCLK: U1.71 (QSPI_SCLK), U2.6 (CLK)
QSPI_SD0: U1.72 (QSPI_SD0), U2.5 (DI(IO0))
QSPI_SD1: U1.74 (QSPI_SD1), U2.2 (DO(IO1))
QSPI_SD2: U1.73 (QSPI_SD2), U2.3 (WP#(IO2))
QSPI_SD3: U1.70 (QSPI_SD3), U2.7 (HOLD#(IO3))
QSPI_SS: R61.1, U1.75 (QSPI_SS), U2.1 (CS#)
SATA0_RX_N: J1.B71 (SATA0_RX_N), J7.43 (SATA-B-(HRX-))
SATA0_RX_P: J1.B70 (SATA0_RX_P), J7.41 (SATA-B+(HRX+))
SATA0_TX_N: J1.A74 (SATA0_TX_N), J7.47 (SATA-A-(HTX-))
SATA0_TX_P: J1.A73 (SATA0_TX_P), J7.49 (SATA-A+(HTX+))
SW_3V3_SB: C5.2, L1.1, U6.2 (SW)
SW_5V_SBY: C9.2, L2.1, U7.2 (SW)
SYS_INT_N: J6.10 (IOB_INT_N), R47.1, U1.26 (GPIO25), U5.3 (ALERT)
THERM_LATCH: Q8.1 (G), U1.27 (GPIO26), U8.5 (Q)
TRIP_N: D4.3 (A), D5.3 (A), R17.1, U8.7 (PRE#)
USB2_FACEP_N: J1.B52 (USB2_FACEP_N), J3.14 (USB2_D-)
USB2_FACEP_P: J1.B51 (USB2_FACEP_P), J3.13 (USB2_D+)
USB2_FACES_N: J1.B77 (USB2_FACES_N), J4.14 (USB2_D-)
USB2_FACES_P: J1.B76 (USB2_FACES_P), J4.13 (USB2_D+)
USB2_MCU_N: J1.B74 (USB2_MCU_N), R63.2
USB2_MCU_P: J1.B73 (USB2_MCU_P), R62.2
USB2_SPARE_N: J1.B80 (USB2_SPARE_N), J6.14 (USB2_LINK_D-)
USB2_SPARE_P: J1.B79 (USB2_SPARE_P), J6.13 (USB2_LINK_D+)
USB_DM_M: R63.1, U1.66 (USB_DM)
USB_DP_M: R62.1, U1.67 (USB_DP)
VIN: C2.1, C3.1, C4.1, C8.1, C12.1, R5.2, R100.2, U5.8 (VBUS), U5.9 (IN-), U6.3 (VIN), U7.3 (VIN)
VIN_F: D3.1 (K), F1.2, R100.1, U5.10 (IN+)
VIN_OR: D1.1 (K), D2.1 (K), F1.1
VREG_AVDD: C35.1, R59.2, U1.61 (VREG_AVDD)
VREG_LX: L3.1, U1.63 (VREG_LX)
XIN: C36.1, U1.30 (XIN), Y1.1 (X1)
XOUT: R60.1, U1.31 (XOUT)
XOUT_C: C37.1, R60.2, Y1.3 (X2)

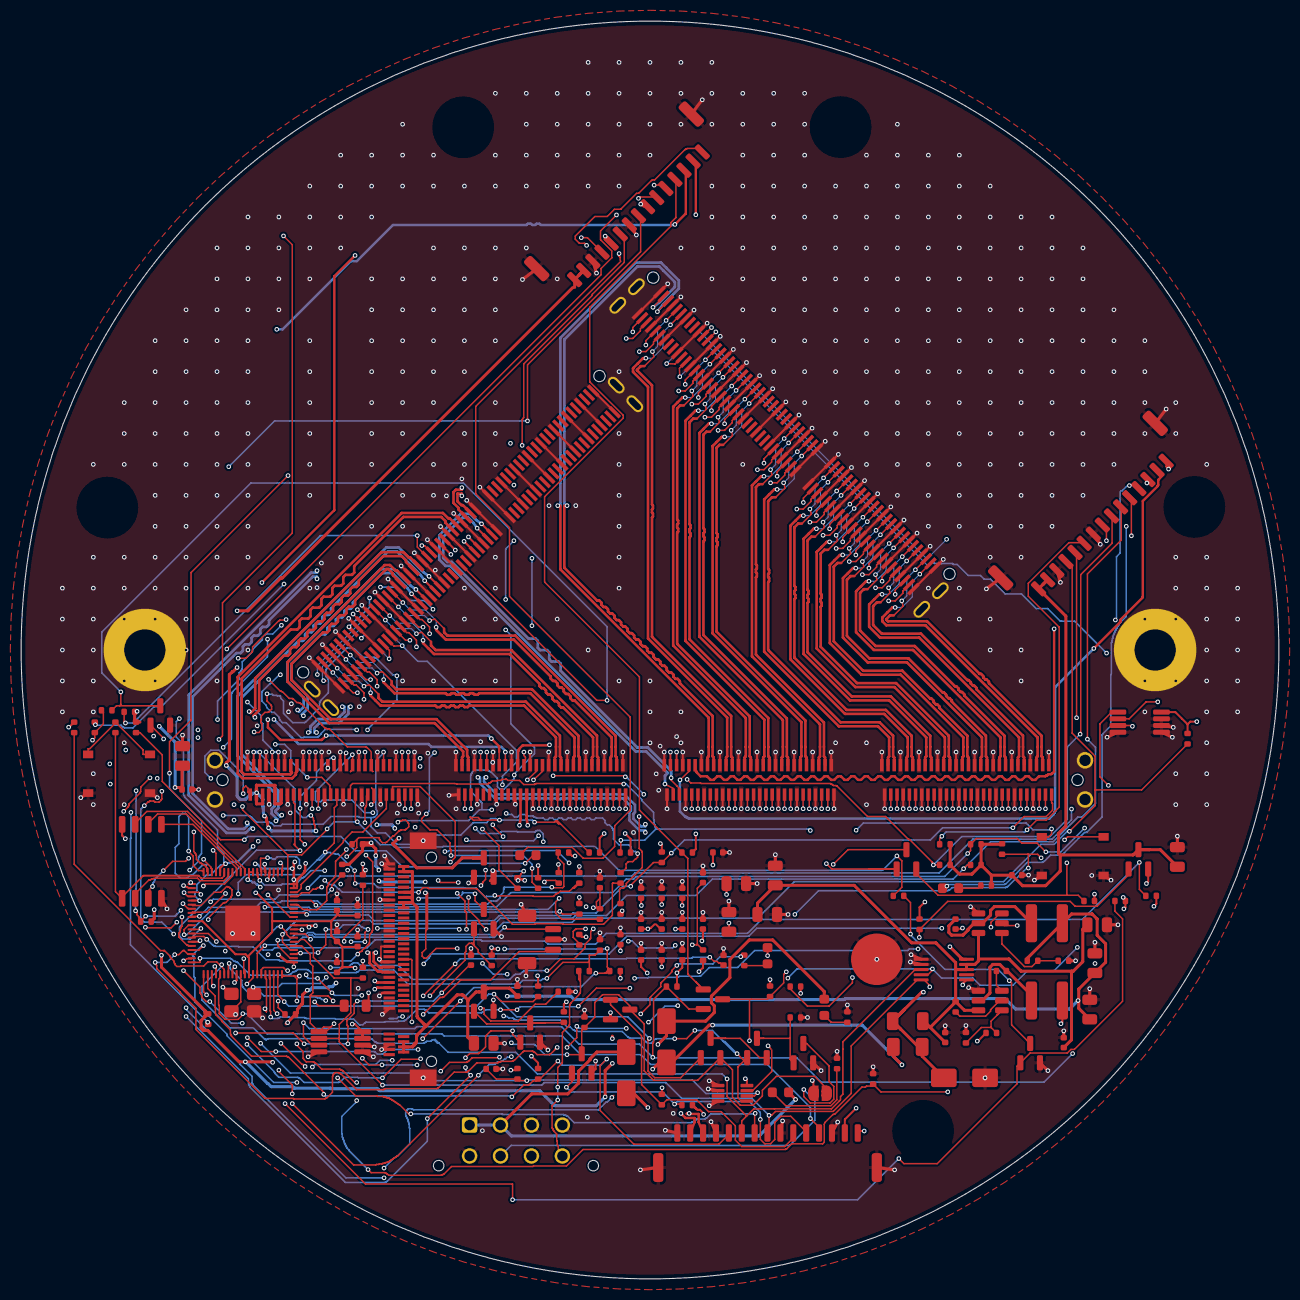
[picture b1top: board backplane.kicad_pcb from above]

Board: 6 copper layers, 122.0 x 122.0 mm, 155 parts (0 on the bottom side), 223 nets.

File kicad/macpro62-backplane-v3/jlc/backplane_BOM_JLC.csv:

Comment,Designator,Footprint,LCSC Part #
100nF 16V X7R 0402,"C1,C12,C14,C16,C19,C21,C22,C23,C24,C25,C26,C27,C28,C32,C33,C34,C35,C38,C39,C5,C8,C9",C_0402_1005Metric,C1525
22uF 25V X5R 0805,"C10,C11,C13,C15,C2,C3,C4,C6,C7",C_0805_2012Metric,C45783
1uF 25V X5R 0402,C20,C_0402_1005Metric,C52923
4.7uF 10V X5R 0402,"C29,C30,C31",C_0402_1005Metric,C23733
15pF 50V C0G 0402,"C36,C37",C_0402_1005Metric,C1548
SS34 3A 40V Schottky SMA,"D1,D2",D_SMA,C8678
LED red 0603,"D10,D6,D7,D8,D9",LED_0603_1608Metric,C2286
SMAJ15A TVS SMA,D3,D_SMA,C113958
BAT54A (LBAT54ALT1G),"D4,D5",SOT-23,C12743
3A 1206 fast fuse (0466003.NRHF class),F1,Fuse_1206_3216Metric,C14165
"ME1022410103011 Mini Cool Edge 224 (C4941560, 0 stock: pre-order)",J1,MP62_CPULINK_MiniCoolEdge_224P_Vertical_SMT_PLACEHOLDER,C4941560
MCIO 124P RA (C4867471) -> Face S x4 + slot B x4 (v3: lanes 4-7 + REFCLK1),J10,MP62_MCIO_124P_RA_SFF-TA-1016,C4867471
Molex 43045-0812 Micro-Fit 2x4 (C277661),J2,Molex_Micro-Fit_3.0_43045-0812_2x04_P3.00mm_Vertical,C277661
BM15B-GHS-TBT (C5305069) Face P AUX,J3,JST_GH_BM15B-GHS-TBT_1x15-1MP_P1.25mm_Vertical,C5305069
BM15B-GHS-TBT (C5305069) Face S AUX,J4,JST_GH_BM15B-GHS-TBT_1x15-1MP_P1.25mm_Vertical,C5305069
BM15B-GHS-TBT (C5305069) IOB-LINK,J6,JST_GH_BM15B-GHS-TBT_1x15-1MP_P1.25mm_Vertical,C5305069
"MCIO 124P RA G97R24332HR class (C4867471, 0 stock: pre-order) -> Face P x16",J9,MP62_MCIO_124P_RA_SFF-TA-1016,C4867471
4.7uH 2A 4x4 (SWPA4030S4R7MT),"L1,L2",L_Changjiang_FNR4030S,C57269
"3.3uH 0806 (FNR201610S3R3MT, RP2350 VREG)",L3,L_0805_2012Metric,C167673
AO3401A P-MOS,"Q1,Q2,Q5,Q6,Q7,Q8",SOT-23,C15127
2N7002 N-MOS,"Q10,Q11,Q12,Q9",SOT-23,C8545
33k 1% 0402,R1,R_0402_1005Metric,C25779
10mR 1% 1W 1206 shunt,R100,R_1206_3216Metric,C105362
100k 1% 0402,"R11,R12,R55",R_0402_1005Metric,C25741
10k 1% 0402,"R13,R14,R15,R16,R17,R18,R19,R2,R20,R21,R23,R24,R25,R26,R29,R30,R33,R34,R35,R36,R39,R4,R40,R42,R43,R44,R45,R46,R47,R48,R49,R65,R7,R8",R_0402_1005Metric,C25744
1k 1% 0402,"R22,R31,R32,R41,R54,R58,R60,R61,R64",R_0402_1005Metric,C11702
2.2k 1% 0402,"R27,R28,R37,R38,R50,R51,R52,R53",R_0402_1005Metric,C25879
56k 1% 0402,R3,R_0402_1005Metric,C25796
"100k 1% 0402 (U6 EN, always on)",R5,R_0402_1005Metric,C25741
10k 1% 0402 (12V LED),R56,R_0402_1005Metric,C25744
10k 1% 0402 (11V_SB LED),R57,R_0402_1005Metric,C25744
33R 1% 0402,"R59,R62,R63",R_0402_1005Metric,C25105
100k 1% 0402 (U7 off until the MCU enables 5V_SBY),R6,R_0402_1005Metric,C25741
BOOTSEL (TS-1187A),SW1,SW_Push_1P1T_XKB_TS-1187A,C318884
BENCH power button (TS-1187A),SW2,SW_Push_1P1T_XKB_TS-1187A,C318884
RP2350B QFN-80 (C42415655),U1,QFN-80-1EP_10x10mm_P0.4mm_EP3.4x3.4mm,C42415655
"W25Q128JVSIQ (C97521, basic)",U2,SOIC-8_5.3x5.3mm_P1.27mm,C97521
TMP1075DGKR @0x48 core side (C2864807),U3,VSSOP-8_3x3mm_P0.65mm,C2864807
TMP1075DGKR @0x49 PSU side (C2864807),U4,VSSOP-8_3x3mm_P0.65mm,C2864807
INA226AIDGSR @0x40 (C49851),U5,VSSOP-10_3x3mm_P0.5mm,C49851
TPS563201DDCR (C116592) -> 3V3_SB,U6,SOT-23-6,C116592
TPS563201DDCR (C116592) -> 5V_SBY,U7,SOT-23-6,C116592
SN74LVC1G74DCUR thermal latch (C70285),U8,VSSOP-8_2.3x2mm_P0.5mm,C70285
12MHz 3225 crystal 20pF,Y1,Crystal_SMD_3225-4Pin_3.2x2.5mm,C9002
